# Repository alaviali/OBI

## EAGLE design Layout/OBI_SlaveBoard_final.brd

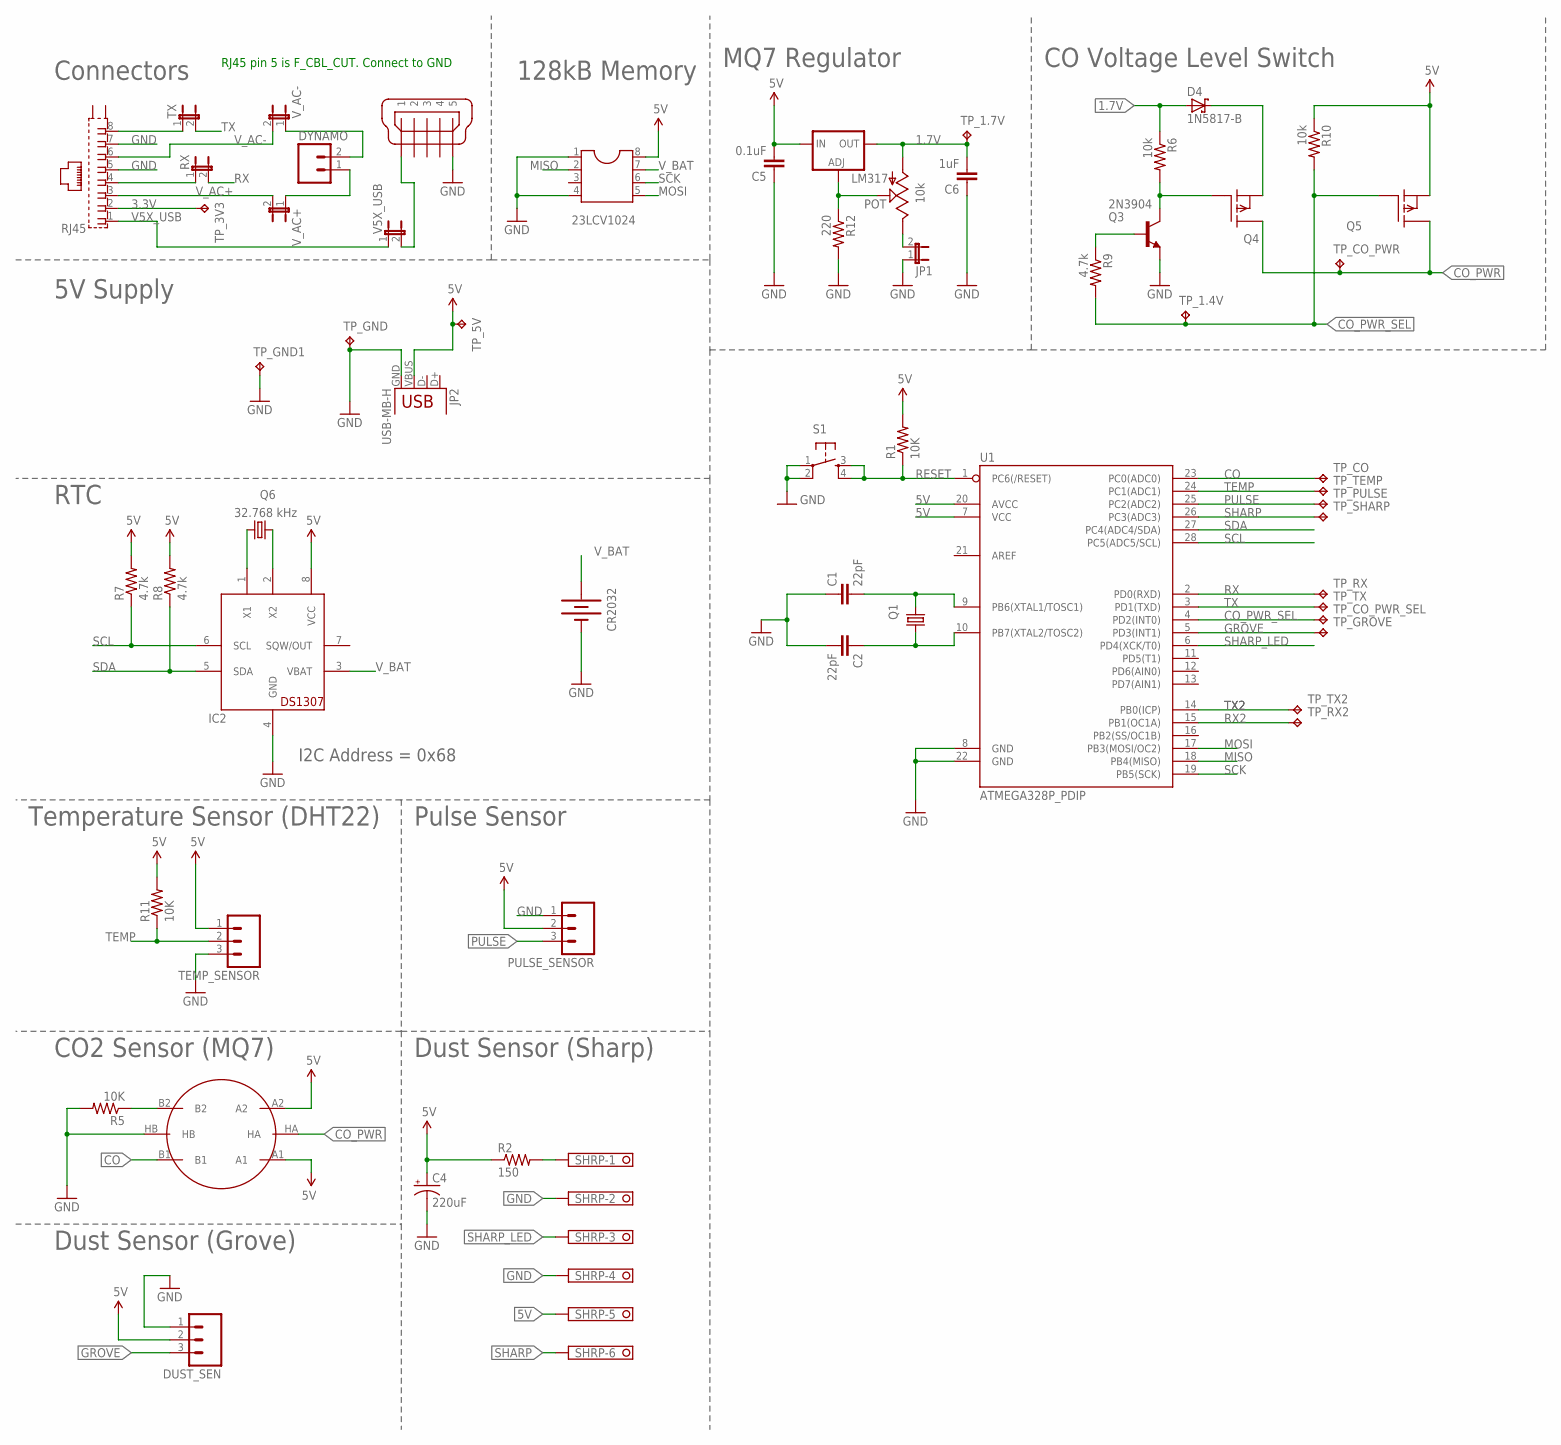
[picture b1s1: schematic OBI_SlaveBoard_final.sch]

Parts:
23LCV1024: DIL8S; SOCKET-08
C1, C2: 22pF; C025-024X044
C4: 220uF; CPOL-RADIAL-10UF-25V
C5: 0.1uF; C025-024X044
C6: 1uF; C025-024X044
CO2_SENSOR: METHANE_SENSOR; MQ-3
CR2032: BATTERY20PTH; BATTCOM_20MM_PTH
D4: 1N5817-B; DO41-10
DUST_SEN: M03SCREW; SCREWTERMINAL-3.5MM-3
DYNAMO: M023.5MM; SCREWTERMINAL-3.5MM-2
IC2: DS1307; DIL08
JP1: JP1E; JP1
JP2: USB-MB-H
LM317: LM317TS; 317TS
MICROB: MICRO-USB-ZX62R-B-5P; ZX62R-B-5P
POT: 10k; CT6
PULSE_SENSOR: M03SCREW; SCREWTERMINAL-3.5MM-3
Q1: CRYSTALHC49S; HC49/S
Q3: 2N3904; TO-92
Q4, Q5: BSS110; TO92
Q6: 32.768 kHz; TC26V
R1, R5, R11: 10K; 0207/2V
R2: 150; 0207/2V
R6, R10: 10k; 0207/2V
R7, R8, R9: 4.7k; 0207/2V
R12: 220; 0207/2V
RJ45: 0446200002
RX: JP1E; JP1
S1: TAC_SWITCHPTH; TACTILE-PTH
SHRP: 1751280
TEMP_SENSOR: M03SCREW; SCREWTERMINAL-3.5MM-3
TP_1.4V, TP_1.7V, TP_3V3, TP_5V: TPPAD1-13; P1-13
TP_CO: TPPAD1-13; P1-13
TP_CO_PWR: TPPAD1-13; P1-13
TP_CO_PWR_SEL: TPPAD1-13; P1-13
TP_GND, TP_GND1: TPPAD1-13; P1-13
TP_GROVE: TPPAD1-13; P1-13
TP_PULSE: TPPAD1-13; P1-13
TP_RX, TP_RX2: TPPAD1-13; P1-13
TP_SHARP: TPPAD1-13; P1-13
TP_TEMP: TPPAD1-13; P1-13
TP_TX, TP_TX2: TPPAD1-13; P1-13
TX: JP1E; JP1
U1: ATMEGA328P_PDIP; DIL28-3
V5X_USB: JP1E; JP1
V_AC+: JP1E; JP1
V_AC-: JP1E; JP1

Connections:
1.7V: C6.2, D4.A, LM317.2 (OUT), POT.A, R6.1, TP_1.7V.TP
3.3V: RJ45.2, TP_3V3.TP
5V: 23LCV1024.8, C4.1 (+), C5.2, CO2_SENSOR.A1, CO2_SENSOR.A2, DUST_SEN.2, IC2.8 (VCC), JP2.VBUS, LM317.3 (IN), PULSE_SENSOR.2, Q5.1 (S), R1.2, R2.1, R7.2, R8.2, R10.1, R11.2, SHRP.5, TEMP_SENSOR.1, TP_5V.TP, U1.7 (VCC), U1.20 (AVCC)
CO: CO2_SENSOR.B1, TP_CO.TP, U1.23 (PC0(ADC0))
CO_PWR: CO2_SENSOR.HA, Q4.3 (D), Q5.3 (D), TP_CO_PWR.TP
CO_PWR_SEL: Q5.2 (G), R9.2, R10.2, TP_1.4V.TP, TP_CO_PWR_SEL.TP, U1.4 (PD2(INT0))
GND: 23LCV1024.1, 23LCV1024.4, C1.1, C2.2, C4.2 (-), C5.1, C6.1, CO2_SENSOR.HB, CR2032.2 (-), DUST_SEN.1, IC2.4 (GND), JP1.1, JP2.GND, MICROB.5, PULSE_SENSOR.1, Q3.1 (E), R5.2, R12.2, RJ45.5, RJ45.7, S1.1, S1.2, SHRP.2, SHRP.4, TEMP_SENSOR.3, TP_GND.TP, TP_GND1.TP, U1.8 (GND), U1.22 (GND)
GROVE: DUST_SEN.3, TP_GROVE.TP, U1.5 (PD3(INT1))
MISO: 23LCV1024.2, U1.18 (PB4(MISO))
MOSI: 23LCV1024.5, U1.17 (PB3(MOSI/OC2))
unnamed: IC2.1 (X1), Q6.1
unnamed: Q3.3 (C), Q4.2 (G), R6.2
unnamed: C1.2, Q1.2, U1.9 (PB6(XTAL1/TOSC1))
unnamed: Q3.2 (B), R9.1
unnamed: C2.1, Q1.1, U1.10 (PB7(XTAL2/TOSC2))
unnamed: IC2.2 (X2), Q6.2
unnamed: RJ45.4, RX.1
unnamed: R2.2, SHRP.1
unnamed: LM317.1 (ADJ), POT.S, R12.1
unnamed: RJ45.8, TX.1
unnamed: DYNAMO.1, V_AC+.1
unnamed: MICROB.1, V5X_USB.2
unnamed: JP1.2, POT.E
unnamed: DYNAMO.2, V_AC-.1
unnamed: D4.C, Q4.1 (S)
unnamed: CO2_SENSOR.B2, R5.1
PULSE: PULSE_SENSOR.3, TP_PULSE.TP, U1.25 (PC2(ADC2))
RESET: R1.1, S1.3, S1.4, U1.1 (PC6(/RESET))
RX: RX.2, TP_RX.TP, U1.2 (PD0(RXD))
RX2: TP_RX2.TP, U1.15 (PB1(OC1A))
SCK: 23LCV1024.6, U1.19 (PB5(SCK))
SCL: IC2.6 (SCL), R7.1, U1.28 (PC5(ADC5/SCL))
SDA: IC2.5 (SDA), R8.1, U1.27 (PC4(ADC4/SDA))
SHARP: SHRP.6, TP_SHARP.TP, U1.26 (PC3(ADC3))
SHARP_LED: SHRP.3, U1.6 (PD4(XCK/T0))
TEMP: R11.1, TEMP_SENSOR.2, TP_TEMP.TP, U1.24 (PC1(ADC1))
TX: TP_TX.TP, TX.2, U1.3 (PD1(TXD))
TX2: TP_TX2.TP, U1.14 (PB0(ICP))
V5X_USB: RJ45.1, V5X_USB.1
V_AC+: RJ45.3, V_AC+.2
V_AC-: RJ45.6, V_AC-.2
V_BAT: 23LCV1024.7, CR2032.1 (+), IC2.3 (VBAT)

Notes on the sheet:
Connectors
5V Supply
RTC
Temperature Sensor (DHT22)
Pulse Sensor
CO2 Sensor (MQ7)
I2C Address = 0x68
Dust Sensor (Sharp)
Dust Sensor (Grove)
128kB Memory
MQ7 Regulator
CO Voltage Level Switch
RJ45 pin 5 is F_CBL_CUT. Connect to GND

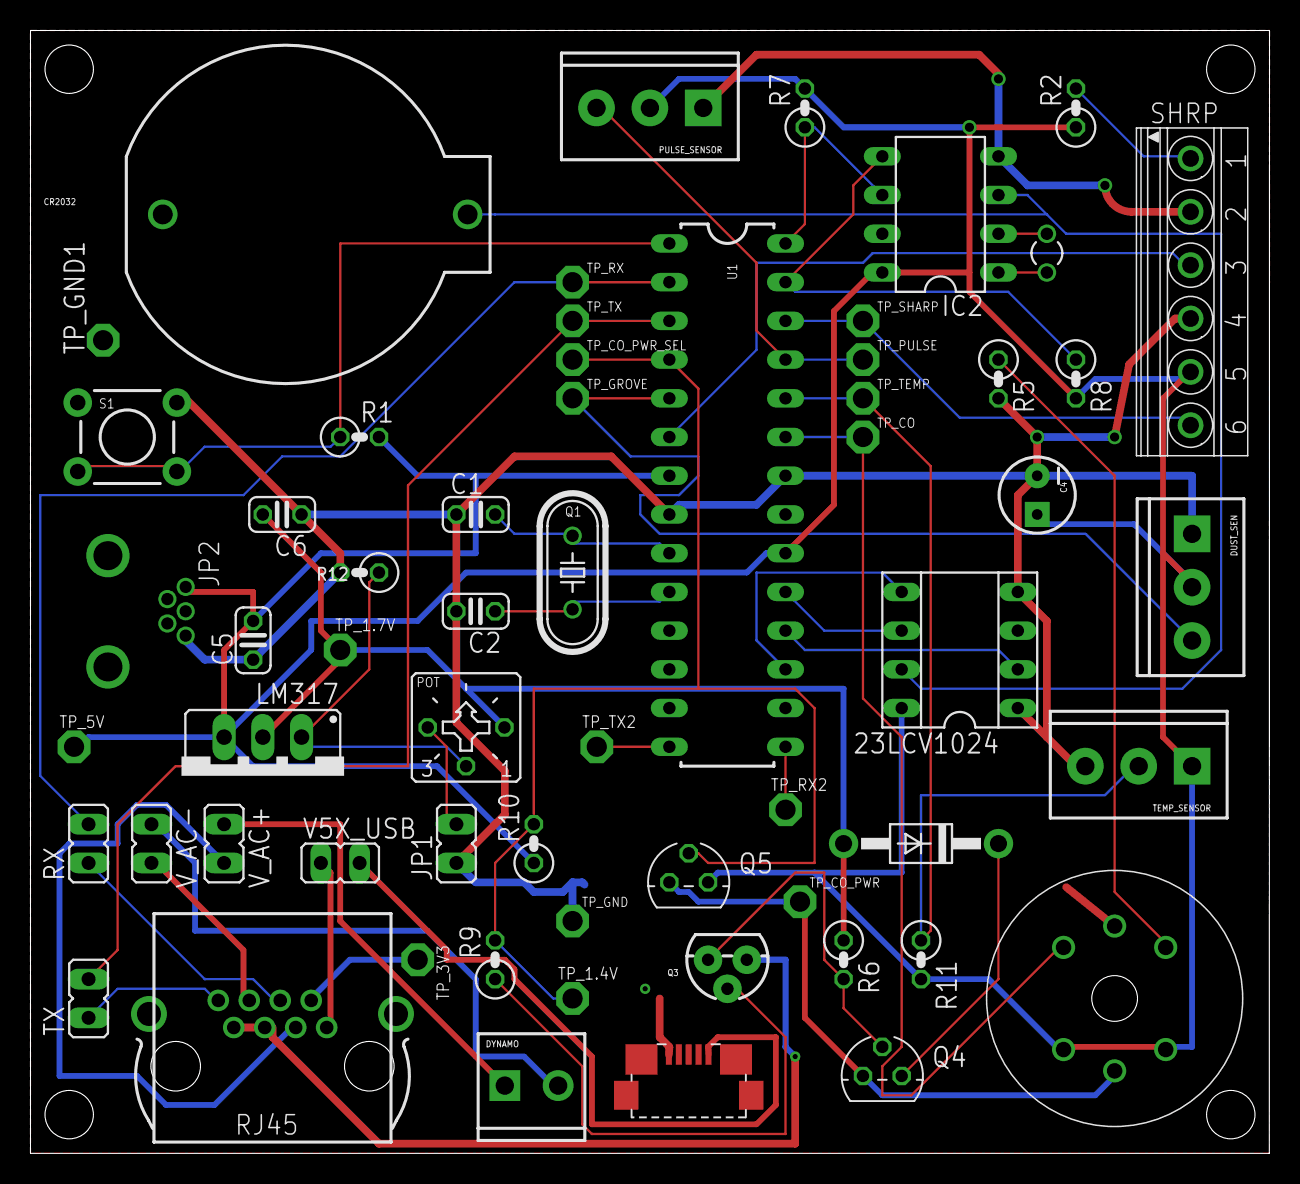
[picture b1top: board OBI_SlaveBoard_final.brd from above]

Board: 2 copper layers, 81.3 x 73.7 mm, 60 parts (0 on the bottom side), 42 nets.

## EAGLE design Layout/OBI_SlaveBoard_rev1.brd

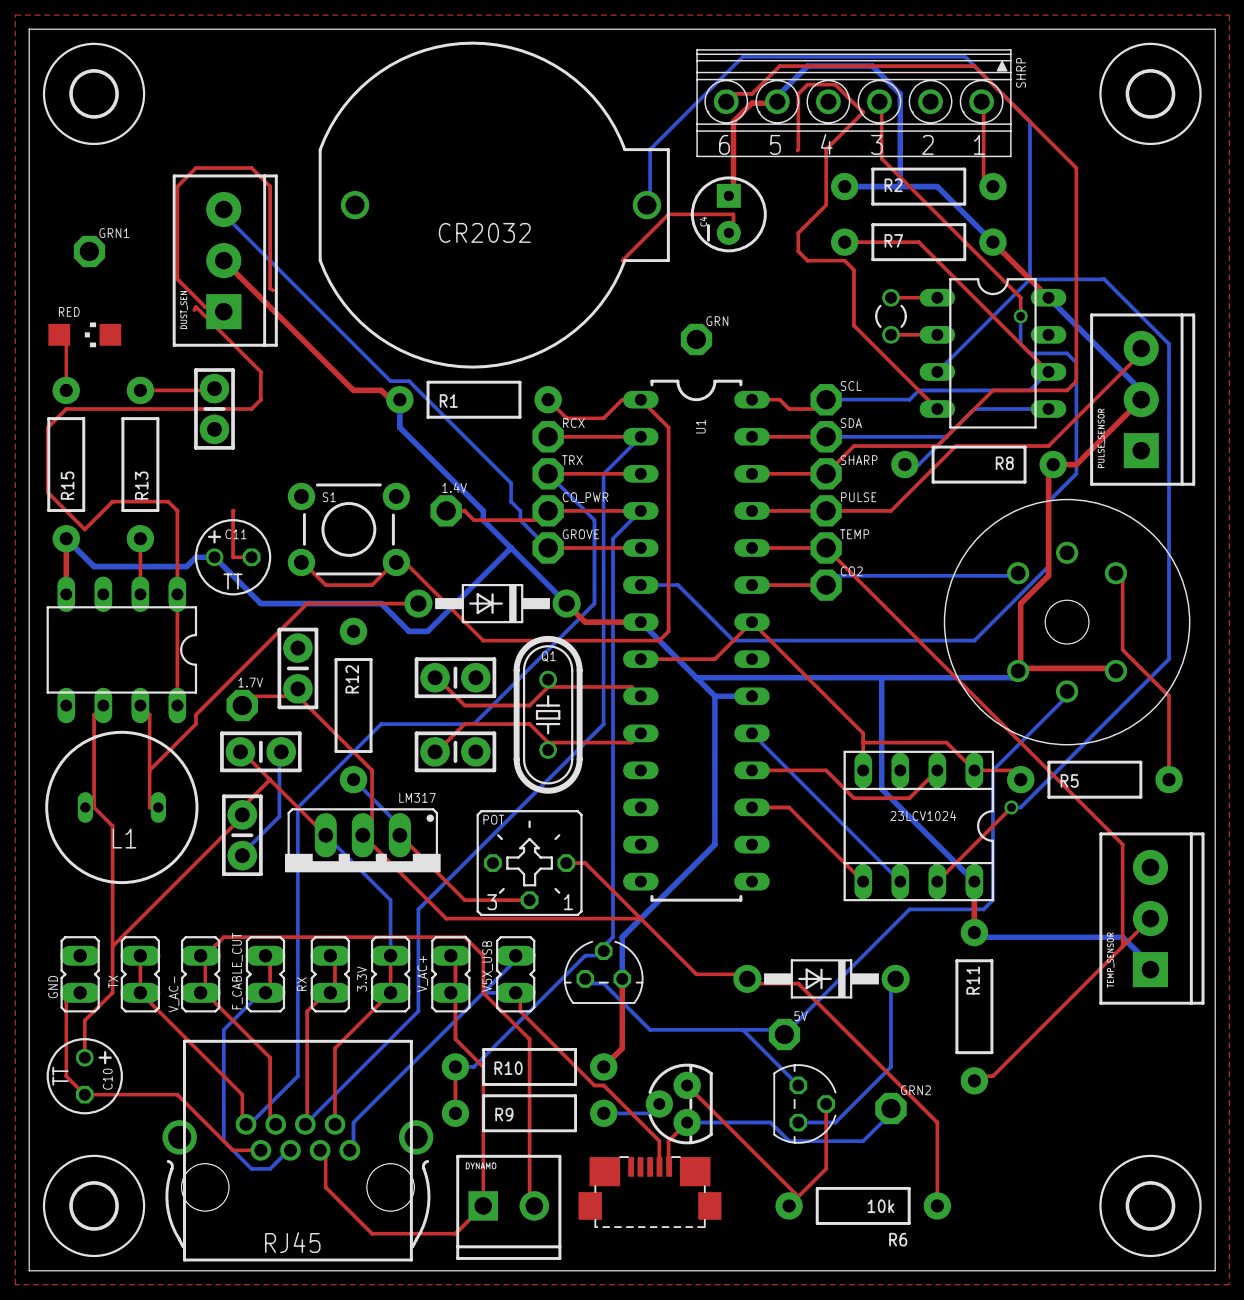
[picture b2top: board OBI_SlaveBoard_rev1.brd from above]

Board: 2 copper layers, 81.3 x 85.1 mm, 75 parts (0 on the bottom side), 39 nets.

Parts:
1.4V, 1.7V, 5V: TPPAD1-13; P1-13
3.3V: JP1
23LCV1024: SOCKET-08
C1, C2: 22pF; CAP-PTH-SMALL-KIT
C4: 220uF; CPOL-RADIAL-10UF-25V
C5, C9: 0.1uF; CAP-PTH-SMALL-KIT
C6: 1uF; CAP-PTH-SMALL-KIT
C8: 0.01uF; CAP-PTH-SMALL-KIT
C10, C11: 100uF; TT2D5
CO2: TPPAD1-13; P1-13
CO2_SENSOR: METHANE_SENSOR; MQ-3
CO_PWR: TPPAD1-13; P1-13
CR2032: BATTCOM_20MM_PTH
D1, D4: 1N5817-B; DO41-10
DUST_SEN: SCREWTERMINAL-3.5MM-3
DYNAMO: SCREWTERMINAL-3.5MM-2
FRAME1: FRAME-LEDGER; CREATIVE_COMMONS
F_CABLE_CUT: JP1
GND: JP1
GRN, GRN1, GRN2: TPPAD1-13; P1-13
GROVE: TPPAD1-13; P1-13
IC2: DS1307; DIL08
L1: 10uH; BS11
LM317: 317TS
MICROB: MICRO-USB-ZX62R-B-5P; ZX62R-B-5P
POT: 10k; CT6
PULSE: TPPAD1-13; P1-13
PULSE_SENSOR: SCREWTERMINAL-3.5MM-3
Q1: HC49/S
Q3: 2N3904; TO-92
Q4, Q5: BSS110; TO92
Q6: 32.768 kHz; TC26V
R1, R5, R11: 10K; AXIAL-0.4
R2: 150; AXIAL-0.4
R6, R10: 10k; AXIAL-0.4
R7, R8, R9: 4.7k; AXIAL-0.4
R12: 220; AXIAL-0.4
R13: 20k; AXIAL-0.4
R15: 180; AXIAL-0.4
RCX: TPPAD1-13; P1-13
RED: CHIPLED_1206
RJ45: 0446200002
RX: JP1
S1: TACTILE-PTH
SCL: TPPAD1-13; P1-13
SDA: TPPAD1-13; P1-13
SHARP: TPPAD1-13; P1-13
SHRP: 1751280
TEMP: TPPAD1-13; P1-13
TEMP_SENSOR: SCREWTERMINAL-3.5MM-3
TRX: TPPAD1-13; P1-13
TX: JP1
U1: ATMEGA328P_PDIP; DIL28-3
U$1, U$2, U$3, U$4: 3,0
V5X_USB: JP1
V_AC+: JP1
V_AC-: JP1
V_BOOST: LT1302; DIL08

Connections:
1.7V: 1.7V.TP, C6.2, D4.A, LM317.2, POT.A, R6.P$1
3.3V: 3.3V.1, 3.3V.2, C5.2, C9.1, C10.+, L1.2, LM317.3, RJ45.2, V_BOOST.6
5V: 23LCV1024.8, C4.1, C11.+, CO2_SENSOR.A1, CO2_SENSOR.A2, D1.C, DUST_SEN.2, IC2.8, PULSE_SENSOR.2, Q5.1, R1.P$2, R2.P$1, R7.P$2, R8.P$2, R10.P$1, R11.P$2, R15.P$2, SHRP.5, TEMP_SENSOR.1, U1.7, U1.20, V_BOOST.4
CO2: CO2.TP, CO2_SENSOR.B1, U1.23
CO_PWR: 5V.TP, CO2_SENSOR.HA, Q4.3, Q5.3
CO_PWR_SEL: 1.4V.TP, CO_PWR.TP, Q5.2, R9.P$2, R10.P$2, U1.4
F_CABLE_CUT: F_CABLE_CUT.1, F_CABLE_CUT.2, RJ45.5
GND: 23LCV1024.1, 23LCV1024.4, C1.1, C2.2, C4.2, C5.1, C6.1, C8.1, C9.2, C10.-, C11.-, CO2_SENSOR.HB, CR2032.2, DUST_SEN.1, GND.1, GND.2, GRN.TP, GRN1.TP, GRN2.TP, IC2.4, MICROB.1, POT.E, PULSE_SENSOR.1, Q3.1, R5.P$2, R12.P$2, RED.C, RJ45.7, S1.1, S1.2, SHRP.2, SHRP.4, TEMP_SENSOR.3, U1.8, U1.22, V_BOOST.1, V_BOOST.8
GROVE: DUST_SEN.3, GROVE.TP, U1.5
MISO: 23LCV1024.2, U1.18
MOSI: 23LCV1024.5, U1.17
unnamed: IC2.1, Q6.1
unnamed: Q3.3, Q4.2, R6.P$2
unnamed: C1.2, Q1.2, U1.9
unnamed: Q3.2, R9.P$1
unnamed: C2.1, Q1.1, U1.10
unnamed: IC2.2, Q6.2
unnamed: R15.P$1, RED.A
unnamed: R2.P$2, SHRP.1
unnamed: LM317.1, POT.S, R12.P$1
unnamed: R13.P$2, V_BOOST.2
unnamed: D4.C, Q4.1
unnamed: CO2_SENSOR.B2, R5.P$1
unnamed: C8.2, R13.P$1
unnamed: D1.A, L1.1, V_BOOST.7
PULSE: PULSE.TP, PULSE_SENSOR.3, U1.25
RESET: R1.P$1, S1.3, S1.4, U1.1
RX: RCX.TP, RJ45.4, RX.1, RX.2, U1.2
SCK: 23LCV1024.6, U1.19
SCL: IC2.6, R7.P$1, SCL.TP, U1.28
SDA: IC2.5, R8.P$1, SDA.TP, U1.27
SHARP: SHARP.TP, SHRP.6, U1.26
SHARP_LED: SHRP.3, U1.6
TEMP: R11.P$1, TEMP.TP, TEMP_SENSOR.2, U1.24
TX: RJ45.8, TRX.TP, TX.1, TX.2, U1.3
V5X_USB: MICROB.2, RJ45.1, V5X_USB.1, V5X_USB.2
V_AC+: DYNAMO.1, RJ45.3, V_AC+.1, V_AC+.2
V_AC-: DYNAMO.2, RJ45.6, V_AC-.1, V_AC-.2
V_BATT: 23LCV1024.7, CR2032.1, IC2.3

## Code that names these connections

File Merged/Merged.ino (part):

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#define SHARP_READ_PIN 3 // Analog PIN 3 ATMEGA 26
int sharp_dust_val = 0;

#define SHARP_LED_PIN 4 // Digital PIN 4 ATMEGA 6
#define SHARP_DELAY_TIME 280 //

// **************** FOR MQ7 SENSOR ****************
#define CO_PWR_SEL_PIN 2    // Digital PIN 2 ATMEGA PIN 4
#define CO_READ_PIN 0       // Analong PIN 0 ATMEGA PIN 23
#define CO_HEAT_TIME 60000  // 60 seconds heat time
#define CO_READ_TIME 90000  // 90 seconds reat time
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
// **************** FOR PULSE SENSOR ****************
//  VARIABLES
#define PULSE_PIN 2                 // Analog PIN 2 ATMEGA 25
volatile int rate[10];                    // array to hold last ten IBI values
volatile unsigned long sampleCounter = 0;          // used to determine pulse timing
volatile unsigned long lastBeatTime = 0;           // used to find IBI
volatile int P = 512;                      // used to find peak in pulse wave, seeded
volatile int T = 512;                     // used to find trough in pulse wave, seeded
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  rtc.begin();  // Make sure clock is running

  // **************** FOR SHARP SENSOR ****************
  pinMode(SHARP_LED_PIN, OUTPUT);

  // **************** FOR GROVE SENSOR ****************
  pinMode(8, INPUT);
  pinMode(13, OUTPUT);

  // **************** FOR MQ7 SENSOR ****************
  pinMode(CO_PWR_SEL_PIN, OUTPUT);
  CO_timer_start = millis();
  turnHeaterHigh();

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  // **************** FOR SHARP SENSOR ****************

  // ledPower is any digital pin on the arduino connected to Pin 3 on the sensor
  digitalWrite(SHARP_LED_PIN, LOW); // power on the LED
  delay(SHARP_DELAY_TIME);  // 280ms
  sharp_dust_val = analogRead(SHARP_READ_PIN); // read the dust value via pin 5 on the sensor
  digitalWrite(SHARP_LED_PIN, HIGH); // turn the LED off

#ifdef DEBUG
  Serial.print(" Sharp value: ");
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void SamplePulse()
{
  pulse_last_sample = millis();
  volatile int Signal = analogRead(PULSE_PIN); // read the Pulse Sensor raw data
  sampleCounter += pulse_sample_delay;        // keep track of the time in mS with this variable
  int N = sampleCounter - lastBeatTime;       // monitor the time since the last beat to avoid noise

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// **************** FOR MQ7 SENSOR ****************
void turnHeaterHigh(){
  // 5v phase
  digitalWrite(CO_PWR_SEL_PIN, LOW);
  heaterInHighPhase = true;
  CO_switch_time = millis() + CO_HEAT_TIME;
}

void turnHeaterLow(){
  // 1.4v phase
  digitalWrite(CO_PWR_SEL_PIN, HIGH);
  heaterInHighPhase = false;
  CO_switch_time = millis() + CO_READ_TIME;
}
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
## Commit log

2015-02-02 Liscence
    Added an MIT liscence
2015-02-03 Alex Bigazzi's Source Code
    The Arduino Source code for the Portland ACE project.
2015-02-21 Test
2015-03-02 Dust sensor code
2015-03-02 CO sensor code
    Working code for CO sensor. Switches the relay for high (60s) and low
    (90s) voltage of the sensor. Also prints the time and the output value..
2015-03-04 Sample code from Adafruit
2015-03-09 Pulse Sensor
    Pulse Sensor Arduino Uno code
2015-03-26 Sharp dust sensor sample code
2015-03-28 Proposal
    Project proposal and proposal presentation
2015-03-30 Rewrote the 2-mode dust sensor code
    Check worklog on Google Drive for more details
2015-03-30 Rewrote the 2-mode Sharp sensor code
    Refer to worklog for more details
2015-04-01 Sharp rewritten, interrupt only, 4s interval
    See worklog in Google Drive for details
2015-04-01 Grove rewritten, interrupt only, 4s interval
    See worklog in Google Drive for details
2015-04-01 MQ7 rewritten, interrupt only, 4s interval
    see worklong in Google Drive for details
2015-04-02 Project Schedule
    Updated the project schedule. Since we're behind and on such a time
    crunch, we need to move fast. Not a whole lot of wiggle room
    unfortunately.
2015-04-02 Schedule+Milestones
    Added milestones to schedule and re-uploaded
2015-04-08 Design Requirements
    Design Requirements Document
2015-04-08 DHT22 rewritten, interrupt only, 4s interval
    See worklog on Google Drive for more details
2015-04-13 Pulse sensor rewritten first draft
    Needs work
2015-04-13 Pulse sensor improved
    prints every 1s, changed timer 2 to timer 1
2015-04-13 1st merge without pulse sensor
2015-04-13 2nd merge without pulse sensor
2015-04-16 Eliminated a few delays
2015-04-16 Added pin setup
2015-04-19 Schematic and Layout
    All the revisions of the schematics and layouts
2015-04-19 images
    pictures of schematic and board
2015-04-19 DL files and more images
    state machine + download files
2015-04-19 state machine
    state machine images
2015-04-20 New pulse sensor code, polling based
2015-04-20 Pulse sensor added
    pulse sensor outputs constant zeros. PIN setup is corrected and
    verified.
2015-04-27 Memory expansion
    test run ok
2015-04-27 Memory code updated
    Problem is in hardware
2015-04-27 Memory tested with Grove sensor
    See worklog for details
2015-05-03 changed a booboo
2015-05-07 Added memory sample code. Added real time clock sample code.
2015-05-07 Added GPS folder
2015-05-11 test commit
2015-05-11 Added libraries directory
2015-05-11 Changed #include "DHT.h" to #include <DHT.h>
2015-05-13 Complete refactoring of Merged.ino code. Added RTC code, serial communication Completed memory code. Had to move sensor reading code out of ISR since RTC code inside the ISR causes the chip to freeze.
2015-05-16 All sensors, GPS and SD card running on frontbox only. GPS uses harware serial because SoftwareSerial corrupts memory operations to either SD or memory chip.
2015-05-17 Added file to libraries directory so compilation can be done using Arduino IDE
2015-05-20 Output formating changes, improved UTC to PDT conversion.
2015-05-27 Version of code running on prototype and box going to DC
2015-06-04 Changed delay for Sharp sensor to microseconds. Modified grove sensor timing.
2015-06-07 documents for wiki
    adjusted requirements, capstone presentation pdf, modified schematic,
    adjusted proposal
2015-06-07 Weekly Reports
    PDF of weekly reports
2015-06-08 UML
    UML pdf upload
2015-06-08 UML images
    Images to display in Wiki for UML
2015-06-08 Test plan, presentation, and images
    Test plan and poster presentation and images being added
2015-06-08 Poster image
    Poster presentation image
2015-06-09 Cleanup and slight modification of grove sensor code.
2015-06-11 Report
    Final Report completed
2015-06-11 Added MS Word version of report with cleaner sentence structure.

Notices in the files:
parts and their libraries:
SparkFun-Capacitors: Licensing: Creative Commons ShareAlike 4.0 International - https://creativecommons.org/licenses/by-sa/4.0
SparkFun-Aesthetics: Released under the Creative Commons Attribution Share-Alike 4.0 License
SparkFun-Aesthetics: https://creativecommons.org/licenses/by-sa/4.0
